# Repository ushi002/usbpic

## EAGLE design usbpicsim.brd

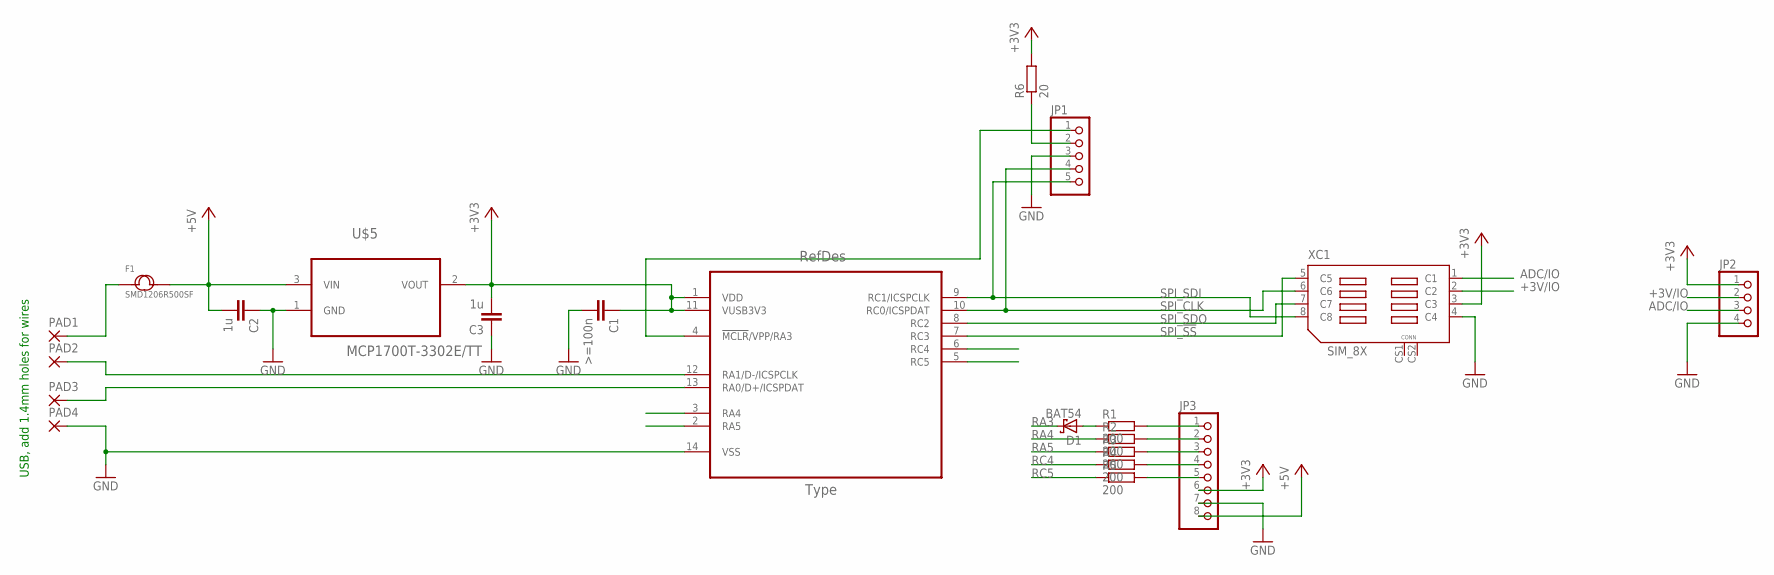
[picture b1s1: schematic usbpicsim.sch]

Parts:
C1: >=100n; C0603
C2, C3: 1u; C0603
D1: BAT54; SOT23
F1: SMD1206R500SF; F1812
JP1: PINHD-1X5; 1X05
JP2: PINHD-1X4; 1X04
JP3: PINHD-1X8; 1X08
PAD1, PAD2, PAD3, PAD4: 1,6/0,9
R1, R2, R3, R4, R5: 200; R0603
R6: 20; R0603
U1: PIC16LF1455-I/ST; SOP65P640X120-14N
U$5: MCP1700T-3302E/TT; SOT95P237X112-3N
XC1: SIM_8X; SIM_8XPADS

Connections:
+3V3: C1.1, C3.2, JP2.1, JP3.6, R6.2, U1.1 (VDD), U1.11 (VUSB3V3), U$5.2 (VOUT), XC1.3 (C3)
+3V/IO: JP2.2, XC1.2 (C2)
+5V: C2.2, F1.2, JP3.8, U$5.3 (VIN)
ADC/IO: JP2.3, XC1.1 (C1)
GND: C1.2, C2.1, C3.1, JP1.3, JP2.4, JP3.7, PAD4.1, U1.14 (VSS), U$5.1 (GND), XC1.4 (C4)
unnamed: JP3.3, R3.2
unnamed: PAD3.1, U1.13 (RA0/D+/ICSPDAT)
unnamed: PAD2.1, U1.12 (RA1/D-/ICSPCLK)
unnamed: JP3.5, R5.2
unnamed: F1.1, PAD1.1
unnamed: JP3.2, R2.2
unnamed: JP3.4, R4.2
unnamed: JP1.2, R6.1
RA3: D1.3 (C), JP1.1, U1.4 (!MCLR!/VPP/RA3)
RA3@1: D1.1 (A), R1.1
RA3@2: JP3.1, R1.2
RA4: R2.1, U1.3 (RA4)
RA5: R3.1, U1.2 (RA5)
RC4: R4.1, U1.6 (RC4)
RC5: R5.1, U1.5 (RC5)
SPI_!SS: U1.7 (RC3), XC1.5 (C5)
SPI_CLK: JP1.4, U1.10 (RC0/ICSPDAT), XC1.6 (C6)
SPI_SDI: JP1.5, U1.9 (RC1/ICSPCLK), XC1.8 (C8)
SPI_SDO: U1.8 (RC2), XC1.7 (C7)

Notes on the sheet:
USB, add 1.4mm holes for wires

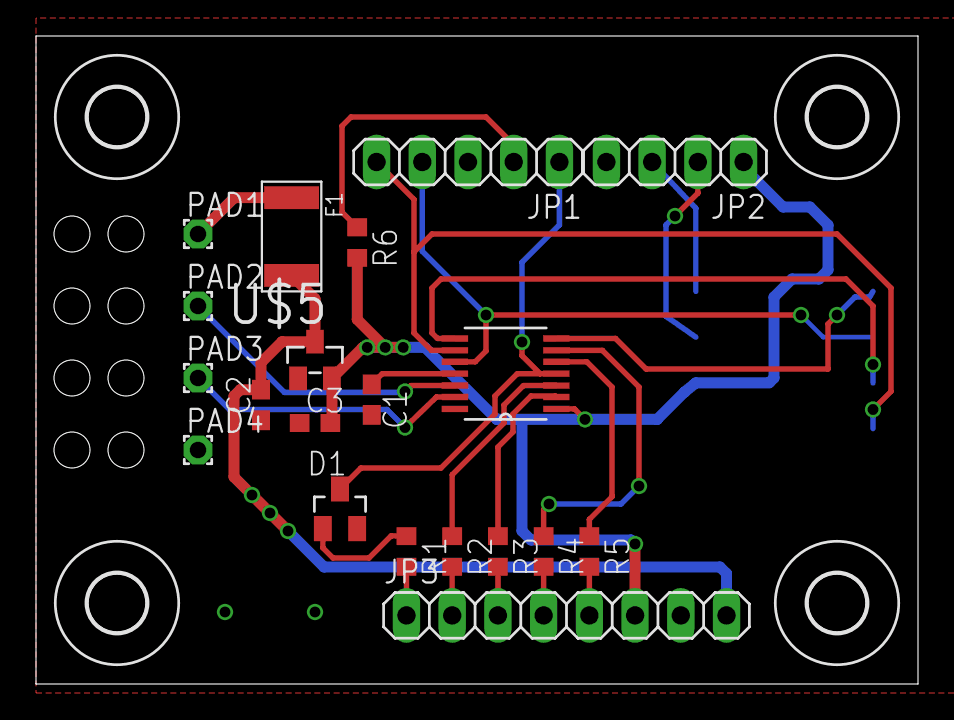
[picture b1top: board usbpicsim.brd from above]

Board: 2 copper layers, 49.0 x 36.0 mm, 25 parts (1 on the bottom side), 24 nets.

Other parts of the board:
U$1, U$2, U$3, U$4: 3,2

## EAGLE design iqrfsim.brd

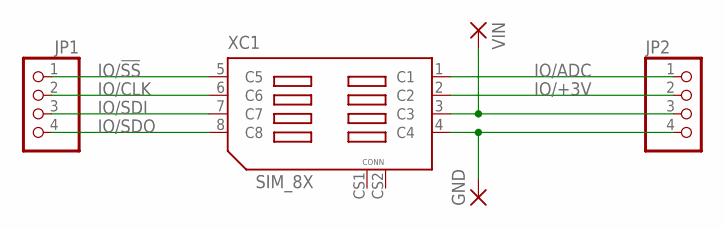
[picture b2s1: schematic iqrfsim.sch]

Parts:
GND: 1,6/0,9
JP1, JP2: PINHD-1X4; 1X04
VIN: 1,6/0,9
XC1: SIM_8X; SIM_8XPADS

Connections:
GND: GND.1, JP2.4, XC1.4 (C4)
IO/!SS: JP1.1, XC1.5 (C5)
IO/+3V: JP2.2, XC1.2 (C2)
IO/ADC: JP2.1, XC1.1 (C1)
IO/CLK: JP1.2, XC1.6 (C6)
IO/SDI: JP1.3, XC1.7 (C7)
IO/SDO: JP1.4, XC1.8 (C8)
VIN: JP2.3, VIN.1, XC1.3 (C3)

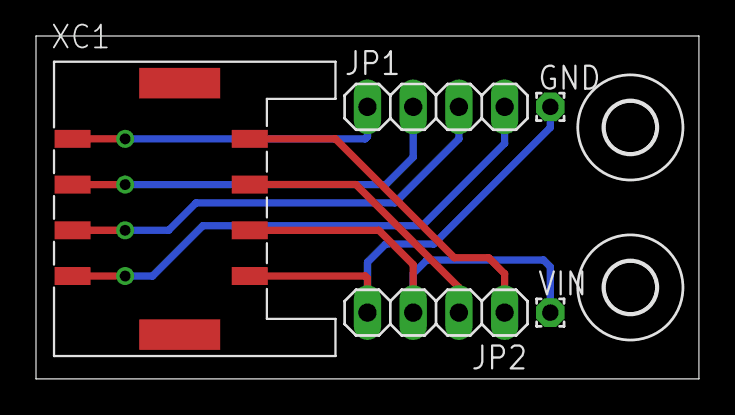
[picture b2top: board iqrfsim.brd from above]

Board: 2 copper layers, 36.8 x 19.1 mm, 7 parts (0 on the bottom side), 8 nets.

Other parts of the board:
U$1, U$2: 2,8

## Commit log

2016-06-15 Use PIC LF (low voltage), add LDO
2016-06-16 Polish scheme, board
2016-06-16 Add usbpicsim board layout
2016-06-16 add IQRF SIM scheme
2016-06-20 Fix iqrfsim sinal names, add board layout
2016-07-11 Finish iqrfsim.brd for manufacture
2016-10-11 More polishing of usbpicsim
2016-10-27 Final usbpicsim board tuning
2016-12-08 version v1.0 - sent to factory
2016-12-09 usbpicsim: improve vias clearance
2017-02-01 add programator pin 1 mark
2017-10-17 Add TODO comment
